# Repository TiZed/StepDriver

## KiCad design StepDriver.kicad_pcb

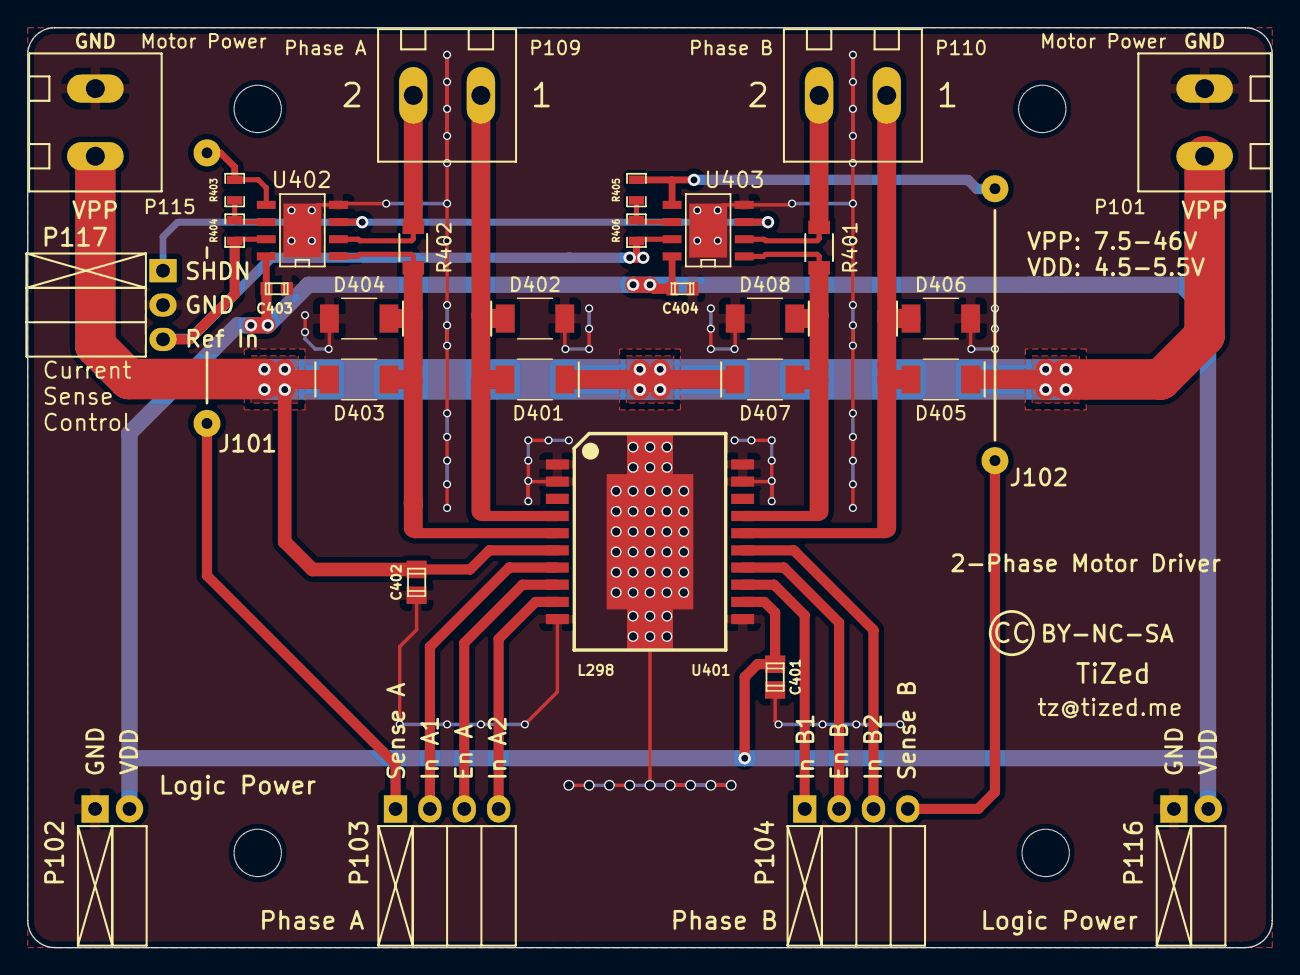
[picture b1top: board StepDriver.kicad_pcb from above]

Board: 2 copper layers, 92.0 x 68.0 mm, 36 parts (0 on the bottom side), 23 nets.

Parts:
C401, C402: 100nF; c_0805
C403, C404: 100nF; c_0603
D401, D402, D403, D404, D405, D406, D407, D408: DIODESCH; SOD-128
J101, J102: 0; WireConnection_0-8mmDrill
P101, P115: Motor Power; Terminal_Block_5mm_2pos
P102, P116: Logic Power; Socket_Strip_Angled_1x02
P103: Phase A; Socket_Strip_Angled_1x04
P104: Phase B; Socket_Strip_Angled_1x04
P109: Phase A; Terminal_Block_5mm_2pos
P110: Phase B; Terminal_Block_5mm_2pos
P117: Cur. Sen. Ctr.; Socket_Strip_Angled_1x03
P118, P119, P121, P122: CONN_01X01; MountingHole_3-5mm
R401, R402: 14m; C_1206
R403, R405: 5.25k; SM0603_Resistor
R404, R406: 1k; SM0603_Resistor
U401: L298; powerso-20
U402, U403: MAX9918/19/20; SO8_WITH_EP

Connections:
/Dual Driver 1/CSA_REFIN: P117.3, R404.2, R406.2, U402.7, U403.7
/Dual Driver 1/CSA_SHDN: P117.1, U402.3, U403.3
/Dual Driver 1/EnA: P103.3, U401.8
/Dual Driver 1/EnB: P104.2, U401.14
/Dual Driver 1/In1: P103.2, U401.7
/Dual Driver 1/In2: P103.4, U401.9
/Dual Driver 1/In3: P104.1, U401.13
/Dual Driver 1/In4: P104.3, U401.15
/Dual Driver 1/Out1: D401.1, D402.2, P109.2, U401.4
/Dual Driver 1/Out2: P109.1, R402.1, U402.2
/Dual Driver 1/Out3: D405.1, D406.2, P110.2, U401.16
/Dual Driver 1/Out4: P110.1, R401.1, U403.2
/Dual Driver 1/SenseA: J101.2, R403.2, U402.5
/Dual Driver 1/SenseB: J102.2, R405.2, U403.5
GND: C401.1, C402.2, C403.2, C404.2, D402.1, D404.1, D406.1, D408.1, P101.1, P102.1, P115.2, P116.1, P117.2, U401.1, U401.2, U401.10, U401.11, U401.19, U401.20, U401.21, U402.4, U402.9, U403.4, U403.9
unnamed: D403.1, D404.2, R402.2, U401.5, U402.1
unnamed: D407.1, D408.2, R401.2, U401.17, U403.1
unnamed: J101.1, P103.1
unnamed: J102.1, P104.4
unnamed: R403.1, R404.1, U402.6
unnamed: R405.1, R406.1, U403.6
VCC: C401.2, C403.1, C404.1, P102.2, P116.2, U401.12, U402.8, U403.8
VPP: C402.1, D401.2, D403.2, D405.2, D407.2, P101.2, P115.1, U401.6

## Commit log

2017-06-20 Added schematic PDF
